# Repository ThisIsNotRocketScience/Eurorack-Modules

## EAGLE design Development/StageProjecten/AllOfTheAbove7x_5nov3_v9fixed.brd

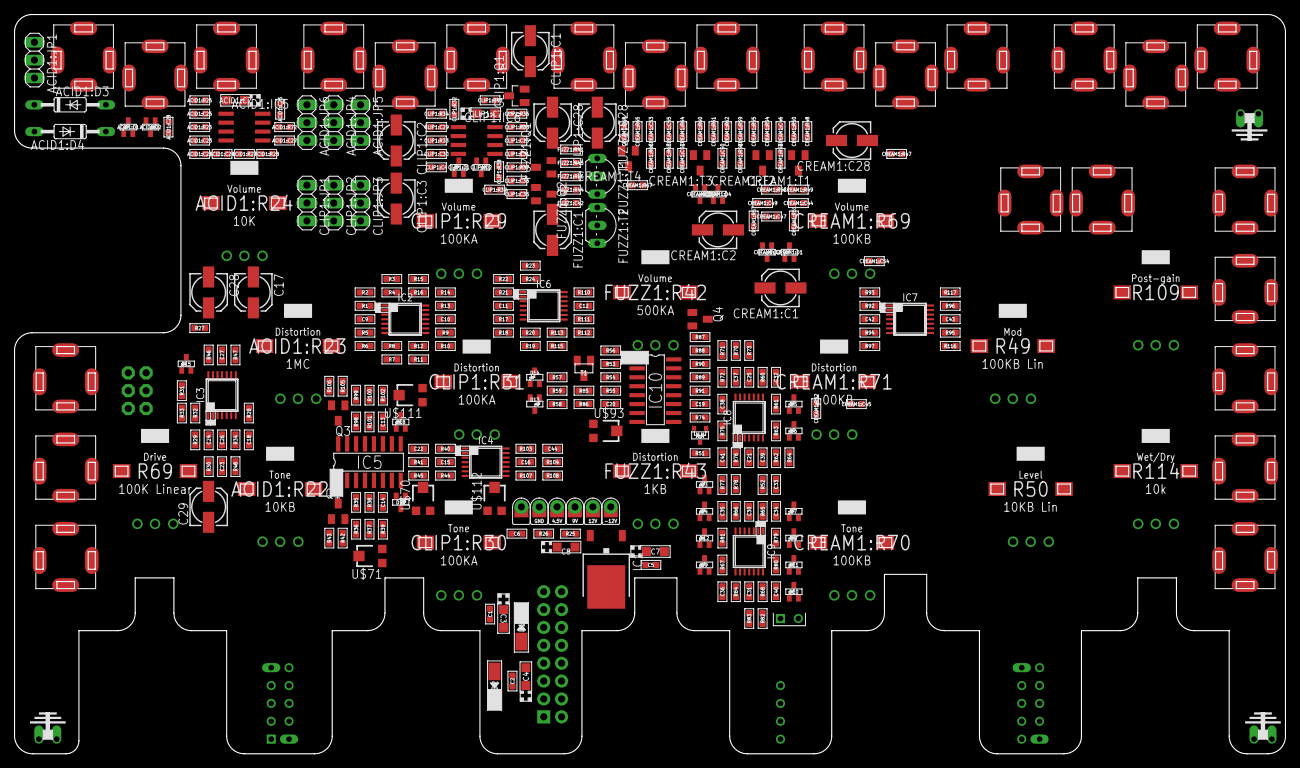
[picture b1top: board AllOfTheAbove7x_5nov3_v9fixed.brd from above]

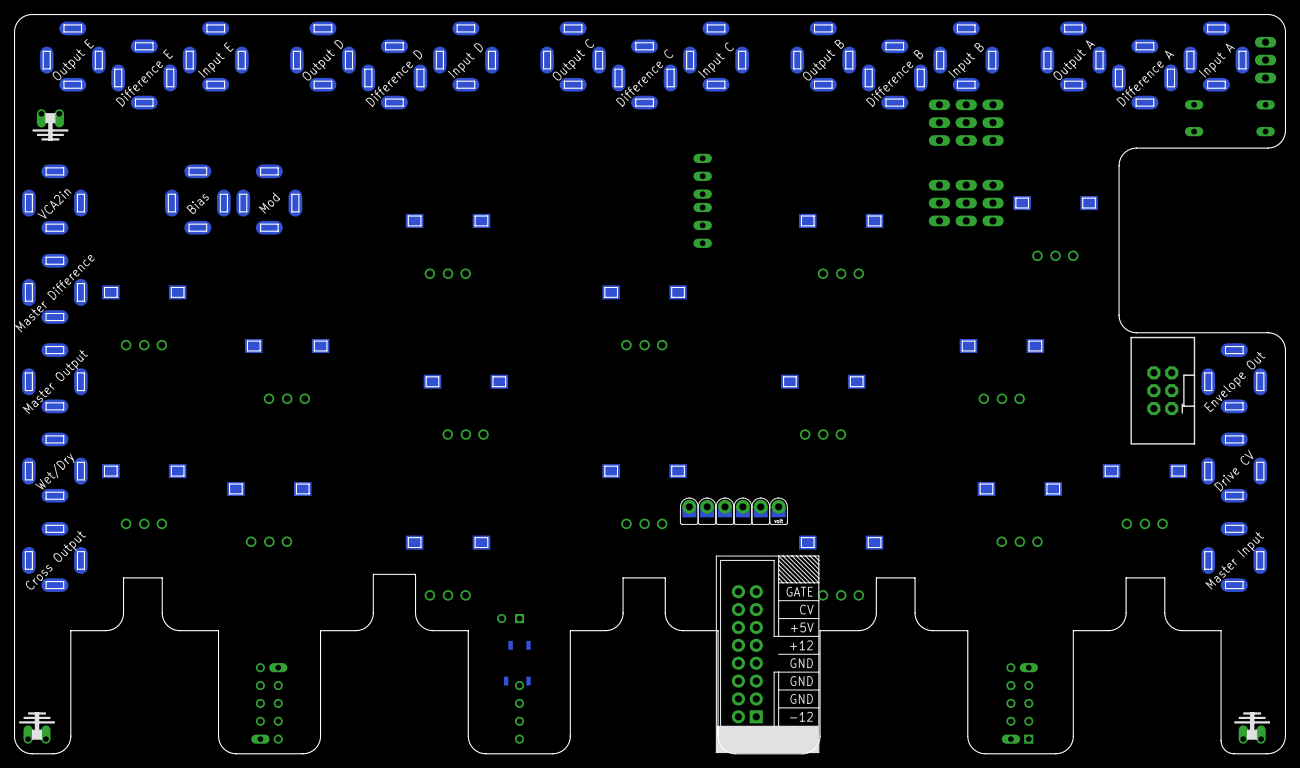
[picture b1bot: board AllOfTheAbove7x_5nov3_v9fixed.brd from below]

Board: 2 copper layers, 180.7 x 105.1 mm, 357 parts (2 on the bottom side), 204 nets, no tracks yet.

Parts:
12V: POWER12V; FENIXINTERNALCONNECTIONPAD
-12V: POWER-12V; FENIXINTERNALCONNECTIONPAD
ACID1:C7: 10uF; CASE-A_3216
ACID1:C22, ACID1:C28: 1nF; C0603
ACID1:C23: 10nF; C0603
ACID1:C24, ACID1:C25: 100n; C0603
ACID1:C26: 47nF; C0603
ACID1:C27: 1uF; C0603
ACID1:D1, ACID1:D2: BAS16W; SOT-323
ACID1:D3, ACID1:D4: 1N4148DO35-10; DO35-10
ACID1:IC5: UA741D; SO08
ACID1:JP1, ACID1:JP4, ACID1:JP5, ACID1:JP6: 1X03
ACID1:R22: 10KB; ALPS_POT_SQUAREHOLES
ACID1:R23: 1MC; ALPS_POT_SQUAREHOLES
ACID1:R24: 10K; ALPS_POT_SQUAREHOLES
ACID1:R25: 10K; R0603
ACID1:R26: 4.7K; R0603
ACID1:R27, ACID1:R72: 1M; R0603
ACID1:R28: 5.6K; R0603
C1, C2, C5, C6, C9, C10, C11, C12, C13, C14, C15, C16, C19, C20, C21, C25, C26, C27, C30, C31, C38, C42, C43: 100n; C0603
C3, C4, C7, C8: 10u; CASE-A_3216
C17, C28, C29: 10uF; 153CLV-0505
C18, C22, C23, C44: 10pF; C0603
C24: 47pF; C0603
C32, C34, C35, C36, C37: 33p; C0603
C33: 220p; C0603
C39: 680n; C0603
C40, C41: 33p FIX; C0603
CLIP1:C1, CLIP1:C3: 4.7uF; 153CLV-0505
CLIP1:C2: 2.2uF; 153CLV-0505
CLIP1:C4, CLIP1:C25: 100n; C0603
CLIP1:C7: 10uF; CASE-A_3216
CLIP1:C28: 1uF; 153CLV-0505
CLIP1:C29, CLIP1:C36: 22nF; C0603
CLIP1:C30: 1nF; C0603
CLIP1:C31: 100pF; C0603
CLIP1:C35: 3.3nF; C0603
CLIP1:D1, CLIP1:D2: BAS16W; SOT-323
CLIP1:IC6: UA741D; SO08
CLIP1:JP1, CLIP1:JP2, CLIP1:JP3: 1X03
CLIP1:Q1: SST201; SOT23
CLIP1:R29, CLIP1:R30, CLIP1:R31: 100KA; ALPS_POT_SQUAREHOLES
CLIP1:R32, CLIP1:R34, CLIP1:R39: 1M; R0603
CLIP1:R33, CLIP1:R37: 1K; R0603
CLIP1:R35: 560R; R0603
CLIP1:R36: 47R; R0603
CLIP1:R38: 1.5K; R0603
CLIP1:R40: 10K; R0603
CREAM1:C1, CREAM1:C2, CREAM1:C28: 1uF; 153CLV-0505
CREAM1:C44, CREAM1:C47, CREAM1:C50: 470pF; C0603
CREAM1:C45: 1uF; C0603
CREAM1:C46, CREAM1:C49, CREAM1:C53, CREAM1:C54: 100nF; C0603
CREAM1:C52: 4nF; C0603
CREAM1:C55: 10nF; C0603
CREAM1:D1, CREAM1:D2, CREAM1:D3, CREAM1:D4: BAS16W; SOT-323
CREAM1:R47, CREAM1:R63: 39K; R0603
CREAM1:R48: 47K; R0603
CREAM1:R49, CREAM1:R56, CREAM1:R61: 470K; R0603
CREAM1:R50: 100R; R0603
CREAM1:R51, CREAM1:R53, CREAM1:R57, CREAM1:R58, CREAM1:R62: 10K; R0603
CREAM1:R52: 1K; R0603
CREAM1:R54, CREAM1:R59, CREAM1:R65: 100K; R0603
CREAM1:R55, CREAM1:R60: 150R; R0603
CREAM1:R64: 22K; R0603
CREAM1:R66: 430K; R0603
CREAM1:R67: 15K; R0603
CREAM1:R68: 3.3K; R0603
CREAM1:R69, CREAM1:R70, CREAM1:R71: 100KB; ALPS_POT_SQUAREHOLES
CREAM1:T1, CREAM1:T2, CREAM1:T3, CREAM1:T4: 2n3904; SOT23-BEC
D1, D2: 1n4001; DO-214AC
D3, D4, D5, D6, D7, D8, D9, D10, D11, D12, D13, D14, D15, D17, D18: BAS16W; SOT-323
FUZZ1:C1: 20uF; 153CLV-0505
FUZZ1:C28: 2.2uF; 153CLV-0505
FUZZ1:C42: 10nF; C0603
FUZZ1:Q1, FUZZ1:Q2: MMBT3906LT1SMD; SOT23-BEC
FUZZ1:R41: 100K; R0603
FUZZ1:R42: 500KA; ALPS_POT_SQUAREHOLES
FUZZ1:R43: 1KB; ALPS_POT_SQUAREHOLES
FUZZ1:R44: 8.2K; R0603
FUZZ1:R45: 33K; R0603
FUZZ1:R46: 470R; R0603
FUZZ1:T1, FUZZ1:T2: TO92-EBC
GND: POWERGND; FENIXINTERNALCONNECTIONPAD
IC1: 7809DT; TO252
IC2, IC3, IC4, IC6, IC7, IC8, IC9: TL074TSSOP14; TSSOP14
IC5, IC10: LM13700M; SO16
J1, J3, J4, J5, J6, J7, J8, J9, J10, J11, J12, J13, J14, J15, J16, J17, J18, J19, J20, J21, J22, J23, J24, J25, J26: JACK; 3.5MM-JACK-SWITCH-13MM-NOHOLES
J2: POWERSHROUDED; POWER_16_SHROUDED
PCB1: EURORACK_PCB5STOMP; EURORACK36HP_5STOMP
Q1, Q3, Q4: MMBT3906LT1SMD; SOT23-BEC
R1, R2, R3, R4, R5, R6, R7, R8, R9, R10, R11, R12, R13, R14, R15, R16, R17, R18, R19, R20, R21, R22, R23, R24, R25, R26, R34, R48, R92, R93, R94, R95, R96, R97, R116, R117: 100k; R0603
R27: 1M; R0603
R28: 150K; R0603
R29, R42, R60, R72, R74, R105: 10K; R0603
R30: 470R; R0603
R31, R41, R47, R104: 1K; R0603
R32, R33, R38, R39, R40, R43, R44, R64, R65, R66, R67, R68, R71, R76, R78, R80, R83, R84, R101, R102, R103, R106, R107: 100K; R0603
R35, R98: 4.7K; R0603
R36, R37, R99, R100: 10R; R0603
R45, R46, R108: 330K; R0603
R49: 100KB Lin; ALPS_POT_SQUAREHOLES
R50: 10KB Lin; ALPS_POT_SQUAREHOLES
R51: 14; R0603
R52, R56: 470K; R0603
R53: 4K7; R0603
R54, R55, R70: 100; R0603
R57: 22K; R0603
R58, R62, R63, R77, R79, R81, R82: 33K; R0603
R59: 4M7; R0603
R61: 47K; R0603
R69: 100K Linear; ALPS_POT_SQUAREHOLES
R73: 220K; R0603
R75: 6K8; R0603
R85: 27k; R0603
R86: 150k; R0603
R87, R88: 1k; R0603
R89, R90: 200k; R0603
R91, R110: 47k; R0603
R109: ALPS_POT_SQUAREHOLES
R111: 2.2k; R0603
R112, R113: 18k; R0603
R114: 10k; ALPS_POT_SQUAREHOLES
R115: 14k; R0603
T1: 3906; SOT23-BEC
U$13, U$15, U$41, U$42, U$43, U$44: VOLTAGETESTPAD; POWERTESTPAD
U$22: 5STOMPBOARD; BYPASSBOARD
U$23: HEADPHONEHOLE_BIGGAP; HEADPHONEHOLE_GAP
U$48, U$49, U$50: GNDLOOP; GROUNDLOOP
U$68: HEADPHONE; 2X3-SHROUDED
U$70, U$71, U$111, U$112: 100k; TC33X
U$74: BAT54S; SOT23
U$92: TESTPOINT_DUAL_PTH; TESTPAD_DUAL_PTH
U$93: 50K; TC33X
WSOUT: SIGNALOUT; FENIXINTERNALCONNECTIONPAD

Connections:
4.5V: ACID1:R72.2, CLIP1:R34.2, R25.1, R26.2, U$44.P$1, U$44.P$2, U$44.P$3
9V: ACID1:JP4.1, C5.2, C7.+, CLIP1:JP2.1, CLIP1:Q1.1, CREAM1:R51.1, CREAM1:R57.1, CREAM1:R62.1, CREAM1:R66.2, CREAM1:R67.2, FUZZ1:C1.+, FUZZ1:Q1.E, FUZZ1:R42.P$1, FUZZ1:R43.P$1, FUZZ1:T1.E, IC1.2, R25.2, U$42.P$1, U$42.P$2, U$42.P$3
12V: 12V.P$1, ACID1:JP4.3, C1.2, C3.+, C6.2, C8.+, C9.2, C11.2, C13.2, C15.2, C19.2, C21.2, C26.2, C30.2, C42.2, CLIP1:JP2.3, D1.2, IC1.1, IC2.4, IC3.4, IC4.4, IC5.11, IC6.4, IC7.4, IC8.4, IC9.4, IC10.11, J21.SWITCH_B@1, J21.SWITCH_T@3, R50.P$3, R115.1, U$13.P$1, U$13.P$2, U$13.P$3, U$22.12V, U$70.3, U$71.3, U$93.1, U$111.3, U$112.3
-12V: -12V.P$1, ACID1:JP5.3, C2.1, C4.-, C10.1, C12.1, C14.1, C16.1, C20.1, C25.1, C27.1, C31.1, C43.1, CLIP1:JP3.3, D2.1, IC2.11, IC3.11, IC4.11, IC5.6, IC6.11, IC7.11, IC8.11, IC9.11, IC10.6, R56.2, R59.1, U$41.P$1, U$41.P$2, U$41.P$3, U$70.1, U$71.1, U$93.3, U$111.1, U$112.1
ACID1:N$2: ACID1:D3.C, ACID1:D4.A, ACID1:JP1.3
ACID1:N$3: ACID1:D1.CATHODE, ACID1:D2.ANODE, ACID1:JP1.1
ACID1:N$20: ACID1:C23.2, ACID1:R25.2
ACID1:N$21: ACID1:IC5.3, ACID1:JP6.2, ACID1:R25.1
ACID1:N$22: ACID1:C26.2, ACID1:IC5.2, ACID1:R27.1
ACID1:N$23: ACID1:C26.1, ACID1:R26.1
ACID1:N$32: ACID1:C27.1, ACID1:IC5.6, ACID1:R27.2
ACID1:N$33: ACID1:R23.P$3, ACID1:R26.2
ACID1:N$34: ACID1:C28.2, ACID1:JP1.2, ACID1:R22.P$3, ACID1:R24.P$3
ACID1:N$35: ACID1:C27.2, ACID1:R28.2
ACID1:N$36: ACID1:R22.P$1, ACID1:R22.P$2, ACID1:R28.1
ACID1:N$81: ACID1:C7.+, ACID1:C25.1, ACID1:IC5.7, ACID1:JP4.2
ACID1:N$82: ACID1:C24.1, ACID1:IC5.4, ACID1:JP5.2
ACID1:TO4.5V: ACID1:JP6.1, ACID1:R72.1
BIASINPUT: J23.TIP_B@1, J23.TIP_T@3, R61.2
BIASMAINLINE: C32.1, D4.ANODE, D6.ANODE, D8.ANODE, D9.ANODE, D10.ANODE, IC8.8, R60.1
CLIP1:N$37: CLIP1:C29.2, CLIP1:JP1.2, CLIP1:R33.1
CLIP1:N$38: CLIP1:C30.2, CLIP1:IC6.3, CLIP1:R33.2
CLIP1:N$39: CLIP1:C7.+, CLIP1:C25.1, CLIP1:IC6.7, CLIP1:JP2.2
CLIP1:N$40: CLIP1:C4.1, CLIP1:IC6.4, CLIP1:JP3.2
CLIP1:N$41: CLIP1:JP1.1, CLIP1:R34.1
CLIP1:N$42: CLIP1:C31.1, CLIP1:IC6.2, CLIP1:R31.P$1, CLIP1:R31.P$2, CLIP1:R35.2, CLIP1:R36.2
CLIP1:N$43: CLIP1:C1.+, CLIP1:C31.2, CLIP1:IC6.6, CLIP1:R31.P$3
CLIP1:N$44: CLIP1:C1.-, CLIP1:R37.1
CLIP1:N$45: CLIP1:D1.CATHODE, CLIP1:D2.ANODE, CLIP1:R30.P$1, CLIP1:R30.P$2, CLIP1:R37.2
CLIP1:N$46: CLIP1:R30.P$3, CLIP1:R38.1
CLIP1:N$47: CLIP1:C2.+, CLIP1:R36.1
CLIP1:N$48: CLIP1:C3.+, CLIP1:R35.1
CLIP1:N$49: CLIP1:C35.1, CLIP1:C36.1, CLIP1:R38.2
CLIP1:N$50: CLIP1:C36.2, CLIP1:Q1.3, CLIP1:R39.2
CLIP1:N$51: CLIP1:C28.+, CLIP1:Q1.2, CLIP1:R40.2
CLIP1:N$52: CLIP1:C28.-, CLIP1:R29.P$3
CREAM1:N$1: CREAM1:C28.-, CREAM1:R47.2
CREAM1:N$61: CREAM1:C28.+, CREAM1:C44.1, CREAM1:R48.2, CREAM1:R49.2, CREAM1:T1.B
CREAM1:N$62: CREAM1:R50.1, CREAM1:T1.E
CREAM1:N$63: CREAM1:C44.2, CREAM1:C45.1, CREAM1:R49.1, CREAM1:R51.2, CREAM1:T1.C
CREAM1:N$64: CREAM1:C45.2, CREAM1:R71.P$3
CREAM1:N$65: CREAM1:C1.-, CREAM1:C47.1, CREAM1:R53.2, CREAM1:R54.2, CREAM1:R56.2, CREAM1:T2.B
CREAM1:N$66: CREAM1:C1.+, CREAM1:D1.ANODE, CREAM1:D2.CATHODE
CREAM1:N$67: CREAM1:R55.2, CREAM1:T2.E
CREAM1:N$68: CREAM1:C47.2, CREAM1:C49.1, CREAM1:D1.CATHODE, CREAM1:D2.ANODE, CREAM1:R56.1, CREAM1:R57.2, CREAM1:T2.C
CREAM1:N$69: CREAM1:C49.2, CREAM1:R58.1
CREAM1:N$70: CREAM1:C2.-, CREAM1:C50.1, CREAM1:R58.2, CREAM1:R59.2, CREAM1:R61.2, CREAM1:T3.B
CREAM1:N$71: CREAM1:R60.2, CREAM1:T3.E
CREAM1:N$72: CREAM1:C50.2, CREAM1:C52.1, CREAM1:D3.ANODE, CREAM1:D4.CATHODE, CREAM1:R61.1, CREAM1:R62.2, CREAM1:R63.1, CREAM1:T3.C
CREAM1:N$73: CREAM1:C53.1, CREAM1:R70.P$2
CREAM1:N$74: CREAM1:C55.2, CREAM1:R63.2, CREAM1:R70.P$1
CREAM1:N$75: CREAM1:C52.2, CREAM1:R64.1, CREAM1:R70.P$3
CREAM1:N$76: CREAM1:C2.+, CREAM1:D3.CATHODE, CREAM1:D4.ANODE
CREAM1:N$77: CREAM1:C53.2, CREAM1:R65.2, CREAM1:R66.1, CREAM1:T4.B
CREAM1:N$78: CREAM1:C54.1, CREAM1:R67.1, CREAM1:T4.C
CREAM1:N$79: CREAM1:R68.2, CREAM1:T4.E
CREAM1:N$80: CREAM1:C54.2, CREAM1:R69.P$3
CREAM1:N$84: CREAM1:R52.1, CREAM1:R71.P$1
CREAM1:N$85: CREAM1:C46.2, CREAM1:R53.1
CREAM1:N$86: CREAM1:C46.1, CREAM1:R71.P$2
CROSSFADER_OUT: IC6.14, J26.TIP_B@1, J26.TIP_T@3, R110.1
CV_IN: J25.TIP_B@1, J25.TIP_T@3, R112.2
ENVELOPE_OUT: J1.SWITCH_B@1, J1.SWITCH_T@3, J24.TIP_B@1, J24.TIP_T@3, R47.1
EURORACK_IN: J20.TIP_B@1, J20.TIP_T@3, R34.1
FUZZ1:N$53: FUZZ1:Q2.E, FUZZ1:R41.1, FUZZ1:R43.P$3, FUZZ1:T2.E
FUZZ1:N$54: FUZZ1:C28.-, FUZZ1:Q1.B, FUZZ1:R41.2, FUZZ1:T1.B
FUZZ1:N$55: FUZZ1:Q1.C, FUZZ1:Q2.B, FUZZ1:R45.2, FUZZ1:T1.C, FUZZ1:T2.B
FUZZ1:N$56: FUZZ1:C1.-, FUZZ1:R43.P$2
FUZZ1:N$57: FUZZ1:C42.2, FUZZ1:R42.P$3
FUZZ1:N$58: FUZZ1:C42.1, FUZZ1:R44.1, FUZZ1:R46.2
FUZZ1:N$59: FUZZ1:Q2.C, FUZZ1:R44.2, FUZZ1:T2.C
GND: ACID1:C7.-, ACID1:C22.2, ACID1:C24.2, ACID1:C25.2, ACID1:C28.1, ACID1:D1.ANODE, ACID1:D2.CATHODE, ACID1:D3.A, ACID1:D4.C, ACID1:JP5.1, ACID1:R23.P$1, ACID1:R23.P$2, ACID1:R24.P$1, C1.1, C2.2, C3.-, C4.+, C5.1, C6.1, C7.-, C8.-, C9.1, C10.2, C11.1, C12.2, C13.1, C14.2, C15.1, C16.2, C17.-, C19.1, C20.2, C21.1, C23.1, C25.2, C26.1, C27.2, C29.-, C30.1, C31.2, C42.1, C43.2, CLIP1:C2.-, CLIP1:C3.-, CLIP1:C4.2, CLIP1:C7.-, CLIP1:C25.2, CLIP1:C30.1, CLIP1:C35.2, CLIP1:D1.ANODE, CLIP1:D2.CATHODE, CLIP1:JP3.1, CLIP1:R29.P$1, CLIP1:R32.2, CLIP1:R39.1, CLIP1:R40.1, CREAM1:C55.1, CREAM1:R48.1, CREAM1:R50.2, CREAM1:R52.2, CREAM1:R54.1, CREAM1:R55.1, CREAM1:R59.1, CREAM1:R60.1, CREAM1:R64.2, CREAM1:R65.1, CREAM1:R68.1, CREAM1:R69.P$1, D3.CATHODE, D5.CATHODE, D7.CATHODE, D11.CATHODE, D12.CATHODE, D13.ANODE, D14.ANODE, FUZZ1:R45.1, FUZZ1:R46.1, GND.P$1, IC1.3, IC4.5, IC4.10, IC5.7, IC5.10, IC6.10, IC6.12, IC7.3, IC7.5, IC7.10, IC7.12, IC8.5, IC8.10, IC10.7, IC10.10, J1.RING_B@1, J1.RING_T@3, J2.3, J2.4, J2.5, J2.6, J2.7, J2.8, J3.RING_B@1, J3.RING_T@3, J4.RING_B@1, J4.RING_T@3, J5.RING_B@1, J5.RING_T@3, J6.RING_B@1, J6.RING_T@3, J7.RING_B@1, J7.RING_T@3, J8.RING_B@1, J8.RING_T@3, J9.RING_B@1, J9.RING_T@3, J10.RING_B@1, J10.RING_T@3, J11.RING_B@1, J11.RING_T@3, J12.RING_B@1, J12.RING_T@3, J13.RING_B@1, J13.RING_T@3, J14.RING_B@1, J14.RING_T@3, J15.RING_B@1, J15.RING_T@3, J16.RING_B@1, J16.RING_T@3, J17.RING_B@1, J17.RING_T@3, J18.RING_B@1, J18.RING_T@3, J19.RING_B@1, J19.RING_T@3, J20.RING_B@1, J20.RING_T@3, J20.SWITCH_B@1, J20.SWITCH_T@3, J21.RING_B@1, J21.RING_T@3, J22.RING_B@1, J22.RING_T@3, J23.RING_B@1, J23.RING_T@3, J23.SWITCH_B@1, J23.SWITCH_T@3, J24.RING_B@1, J24.RING_T@3, J25.RING_B@1, J25.RING_T@3, J25.SWITCH_B@1, J25.SWITCH_T@3, J26.RING_B@1, J26.RING_T@3, R1.2, R5.2, R9.2, R13.2, R17.2, R21.2, R26.1, R27.1, R28.1, R36.1, R37.2, R39.2, R42.1, R46.1, R49.P$1, R50.P$1, R51.2, R52.2, R54.1, R55.1, R69.P$1, R72.2, R73.1, R74.1, R87.1, R88.1, R99.1, R100.2, R102.2, R105.1, R109.P$1, R114.P$1, U$22.GND, U$22.GND2, U$22.GND3, U$43.P$1, U$43.P$2, U$43.P$3, U$48.P$1, U$48.P$2, U$49.P$1, U$49.P$2, U$50.P$1, U$50.P$2, U$68.3, U$68.4, U$92.P$2
GUITAR_IN: C28.-, R27.2, U$68.5, U$68.6
GUITAR_OUT: R31.2, R32.2, U$15.P$1, U$15.P$2, U$15.P$3
INPUT_A: J6.TIP_B@1, J6.TIP_T@3, R2.2, U$22.P$3
INPUT_B: J4.TIP_B@1, J4.TIP_T@3, R6.2, U$22.P$7
INPUT_C: J11.TIP_B@1, J11.TIP_T@3, R10.2, U$22.P$11
INPUT_D: J14.TIP_B@1, J14.TIP_T@3, R14.2, U$22.P$15
INPUT_E: J17.TIP_B@1, J17.TIP_T@3, R22.2, U$22.P$19
INPUT_WS: R85.2, U$22.P$20
MIX_OUT: D15.ANODE, IC3.8, IC3.9, R35.1
unnamed: IC7.2, R92.2, R93.1
unnamed: D1.1, J2.9, J2.10
unnamed: D2.2, J2.1, J2.2
unnamed: ACID1:C22.1, ACID1:C23.1, U$22.P$4
unnamed: ACID1:R24.P$2, U$22.P$2
unnamed: IC7.1, J7.TIP_B@1, J7.TIP_T@3, R93.2
unnamed: CLIP1:C29.1, CLIP1:R32.1, U$22.P$8
unnamed: FUZZ1:C28.+, U$22.P$12
unnamed: FUZZ1:R42.P$2, U$22.P$10
unnamed: CREAM1:R47.1, U$22.P$16
unnamed: CREAM1:R69.P$2, U$22.P$14
unnamed: CLIP1:R29.P$2, U$22.P$6
unnamed: IC7.6, R94.2, R97.1
unnamed: C23.2, C28.+, IC3.3, R28.2
unnamed: IC2.3, R1.1, R2.1
unnamed: IC6.9, R111.2, R112.1, R113.1
unnamed: C24.1, IC3.1, R29.2, R31.1
unnamed: IC2.1, J8.TIP_B@1, J8.TIP_T@3, R4.1
unnamed: IC2.5, R5.1, R6.1
unnamed: IC2.6, R7.1, R8.2
unnamed: Q4.E, R111.1
unnamed: IC6.8, Q4.B
unnamed: IC2.7, J5.TIP_B@1, J5.TIP_T@3, R8.1
unnamed: IC2.10, R9.1, R10.1
unnamed: IC2.9, R11.1, R12.2
unnamed: R114.P$3, R115.2
unnamed: R113.2, R114.P$2
unnamed: IC2.8, J12.TIP_B@1, J12.TIP_T@3, R12.1
unnamed: IC2.12, R13.1, R14.1
unnamed: IC2.13, R15.1, R16.2
unnamed: IC7.7, J9.TIP_B@1, J9.TIP_T@3, R97.2
unnamed: IC7.9, R95.2, R116.1
unnamed: IC2.14, J15.TIP_B@1, J15.TIP_T@3, R16.1
unnamed: IC6.5, R17.1, R18.1
unnamed: IC6.6, R19.1, R20.2
unnamed: IC7.8, J13.TIP_B@1, J13.TIP_T@3, R116.2
unnamed: IC7.13, R96.2, R117.1
unnamed: IC6.7, J10.TIP_B@1, J10.TIP_T@3, R20.1
unnamed: IC6.3, R21.1, R22.1
unnamed: IC6.2, R23.1, R24.2
unnamed: IC7.14, J16.TIP_B@1, J16.TIP_T@3, R117.2
unnamed: IC6.1, J18.TIP_B@1, J18.TIP_T@3, R24.1
unnamed: C24.2, IC3.2, R29.1, R30.2
unnamed: C29.+, R30.1
unnamed: C18.2, IC3.7, R33.2, R48.2
unnamed: IC3.5, R34.2
unnamed: IC5.4, R37.1, R38.1
unnamed: IC5.3, R35.2, R36.2
unnamed: IC4.3, IC5.5, R39.1
unnamed: C22.1, IC4.2, R40.1
unnamed: C22.2, IC4.1, R40.2, R41.1
unnamed: R38.2, U$71.2
unnamed: D17.ANODE, IC4.7, Q1.B
unnamed: D17.CATHODE, IC4.6, R43.1, R44.2, R45.2
unnamed: Q1.E, R42.2, R43.2
unnamed: IC5.1, Q1.C
unnamed: R45.1, U$70.2
unnamed: R44.1, R69.P$2
unnamed: IC3.13, IC3.14, R47.2
unnamed: C17.+, D15.CATHODE, IC3.12, R46.2
unnamed: C18.1, IC3.6, R48.1
unnamed: R51.1, U$74.P$3
unnamed: C32.2, IC8.9, R60.2, R61.1
unnamed: R49.P$2, R57.2
unnamed: J22.TIP_B@1, J22.TIP_T@3, R49.P$3
unnamed: D14.CATHODE, R57.1, R58.1, R59.2, T1.E
unnamed: R50.P$2, R58.2
unnamed: C38.2, R74.2, R75.2, U$74.P$1, U$74.P$2
unnamed: C33.1, IC8.7, R62.1, R63.2, R64.2
unnamed: C33.2, C39.2, IC8.6, R62.2
unnamed: C39.1, IC10.5, R52.1
unnamed: D5.ANODE, D6.CATHODE, IC9.3, R63.1
unnamed: C34.1, IC9.1, R65.1, R79.2, R80.2
unnamed: D7.ANODE, D8.CATHODE, IC9.5, R79.1
unnamed: C34.2, IC9.2, R64.1, R65.2
unnamed: C35.2, IC9.6, R66.2, R80.1
unnamed: C35.1, IC9.7, R66.1, R67.2, R81.2
unnamed: D9.CATHODE, D12.ANODE, IC9.10, R81.1
unnamed: C36.1, IC9.8, R82.2, R83.2, R84.1
unnamed: C36.2, IC9.9, R67.1, R84.2
unnamed: D10.CATHODE, D11.ANODE, IC9.12, R82.1
unnamed: C40.2, IC9.13, R68.2, R83.1
unnamed: C40.1, IC9.14, R68.1, R77.1, R78.1
unnamed: D3.ANODE, D4.CATHODE, IC8.3, R77.2
unnamed: C41.2, IC8.2, R76.1, R78.2
unnamed: C41.1, IC8.1, R75.1, R76.2, U$92.P$1
unnamed: C38.1, IC8.12, R73.2
unnamed: C37.1, IC8.14, R70.2
unnamed: C37.2, IC8.13, R71.2, R72.1
unnamed: D13.CATHODE, R56.1, T1.B
unnamed: R53.1, T1.C
unnamed: IC10.1, R53.2
unnamed: IC10.3, R54.2, R85.1
unnamed: R86.2, U$93.2
unnamed: IC10.4, R55.2, R86.1
unnamed: IC10.13, R87.2, R89.1
unnamed: IC10.14, R88.2, R90.1
unnamed: IC5.13, R100.1, R101.1
unnamed: IC5.14, R98.2, R99.2
unnamed: IC4.12, IC5.12, R102.1
unnamed: C44.1, IC4.13, R103.1
unnamed: C44.2, IC4.14, R103.2, R104.1
unnamed: R101.2, U$111.2
unnamed: D18.ANODE, IC4.8, Q3.B
unnamed: D18.CATHODE, IC4.9, R106.1, R107.2, R108.2
unnamed: Q3.E, R105.2, R106.2
unnamed: IC5.16, Q3.C
unnamed: R108.1, U$112.2
unnamed: R107.1, R109.P$2
unnamed: IC2.2, R3.1, R4.2
OTA_CONTROL: IC10.16, Q4.C
OTA_OUT: IC6.13, IC10.12, R91.2, R110.2
OUTPUT_A: J4.SWITCH_B@1, J4.SWITCH_T@3, R3.2, R92.1, U$22.P$1
OUTPUT_B: J11.SWITCH_B@1, J11.SWITCH_T@3, R7.2, R94.1, U$22.P$5
OUTPUT_C: J14.SWITCH_B@1, J14.SWITCH_T@3, R11.2, R95.1, U$22.P$9
OUTPUT_D: J17.SWITCH_B@1, J17.SWITCH_T@3, R15.2, R96.1, U$22.P$13
OUTPUT_E: R23.2, R98.1, U$22.P$17
OUTPUT_WS: R70.1, R71.1, U$22.P$18, WSOUT.P$1
VCA_CV_IN1: J21.TIP_B@1, J21.TIP_T@3, R69.P$3
VCA_CV_IN2: J1.TIP_B@1, J1.TIP_T@3, R109.P$3
VCA_OUTPUT1: J6.SWITCH_B@1, J6.SWITCH_T@3, R18.2, R41.2, R90.2
VCA_OUTPUT2: J3.TIP_B@1, J3.TIP_T@3, R19.2, R89.2, R91.1, R104.2
VCA_SIG_IN: IC3.10, R32.1, R33.1

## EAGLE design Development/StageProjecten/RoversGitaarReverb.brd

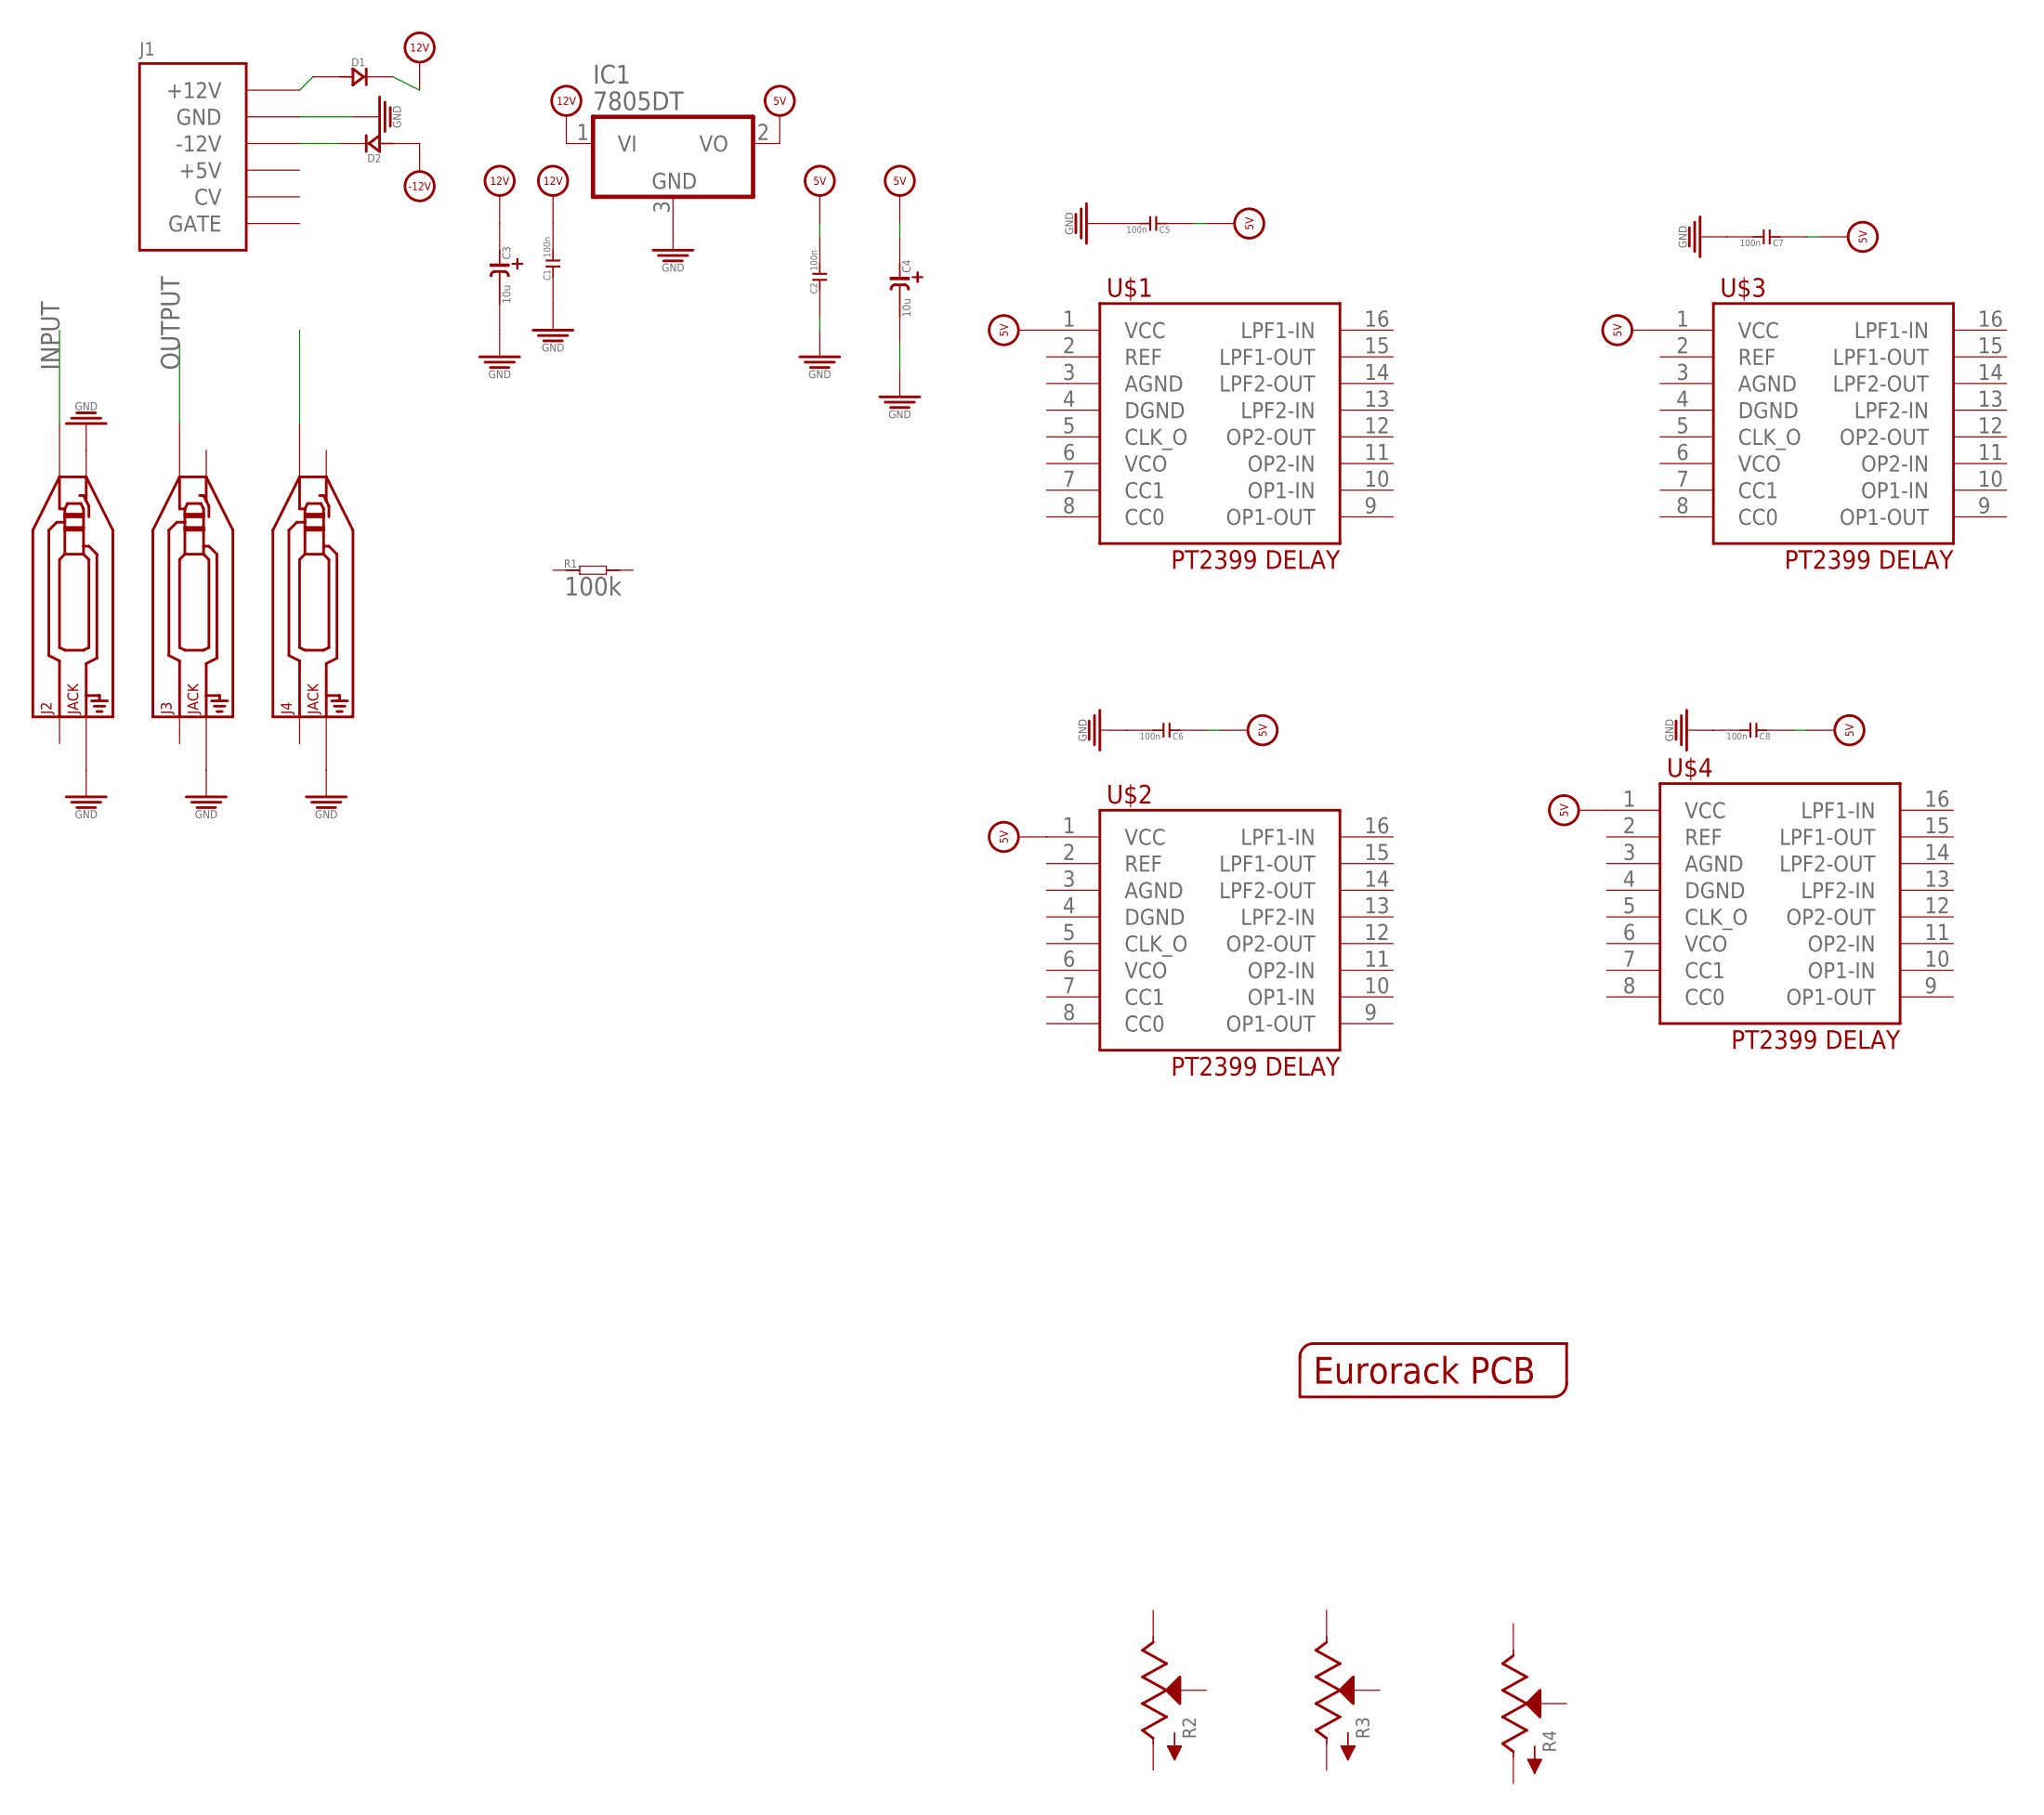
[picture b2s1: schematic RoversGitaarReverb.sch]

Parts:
C1, C2, C5, C6, C7, C8: 100n; C0603
C3, C4: 10u; CASE-A_3216
D1, D2: D-SMA; DO-214AC
IC1: 7805DT; TO252
J1: POWERSHROUDED; POWER_16_SHROUDED
J2, J3, J4: JACK; 3.5MM-JACK-SWITCH-13MM-NOHOLES
PCB1: EURORACK_PCB12HP; EURORACK12HPPCB
R1: 100k; R0603
R2, R3, R4: POTSQUAREHOLE_SMALLKNOB; ALPS_POT_SQUAREHOLES
U$1, U$2, U$3, U$4: PT2399; SO16

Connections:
5V: C2.2, C4.+ (1), C5.1, C6.1, C7.1, C8.1, IC1.2 (VO), U$1.1 (VCC), U$2.1 (VCC), U$3.1 (VCC), U$4.1 (VCC)
12V: C1.2, C3.+ (1), D1.2 (-), IC1.1 (VI)
-12V: D2.1 (+)
GND: C1.1, C2.1, C3.- (2), C4.- (2), C5.2, C6.2, C7.2, C8.2, IC1.3 (GND), J1.3 (GND), J1.4 (GND), J1.5 (GND), J1.6 (GND), J1.7 (GND), J1.8 (GND), J2.RING_B@1 (RING), J2.RING_T@3 (RING), J2.SWITCH_B@1 (SWITCH), J2.SWITCH_T@3 (SWITCH), J3.RING_B@1 (RING), J3.RING_T@3 (RING), J4.RING_B@1 (RING), J4.RING_T@3 (RING)
INPUT: J2.TIP_B@1 (TIP), J2.TIP_T@3 (TIP)
unnamed: D1.1 (+), J1.9 (+12V), J1.10 (+12V)
unnamed: D2.2 (-), J1.1 (-12V), J1.2 (-12V)
unnamed: J4.TIP_B@1 (TIP), J4.TIP_T@3 (TIP)
OUTPUT: J3.TIP_B@1 (TIP), J3.TIP_T@3 (TIP)

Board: 2 copper layers, 24 parts (1 on the bottom side), 8 nets, no tracks yet.

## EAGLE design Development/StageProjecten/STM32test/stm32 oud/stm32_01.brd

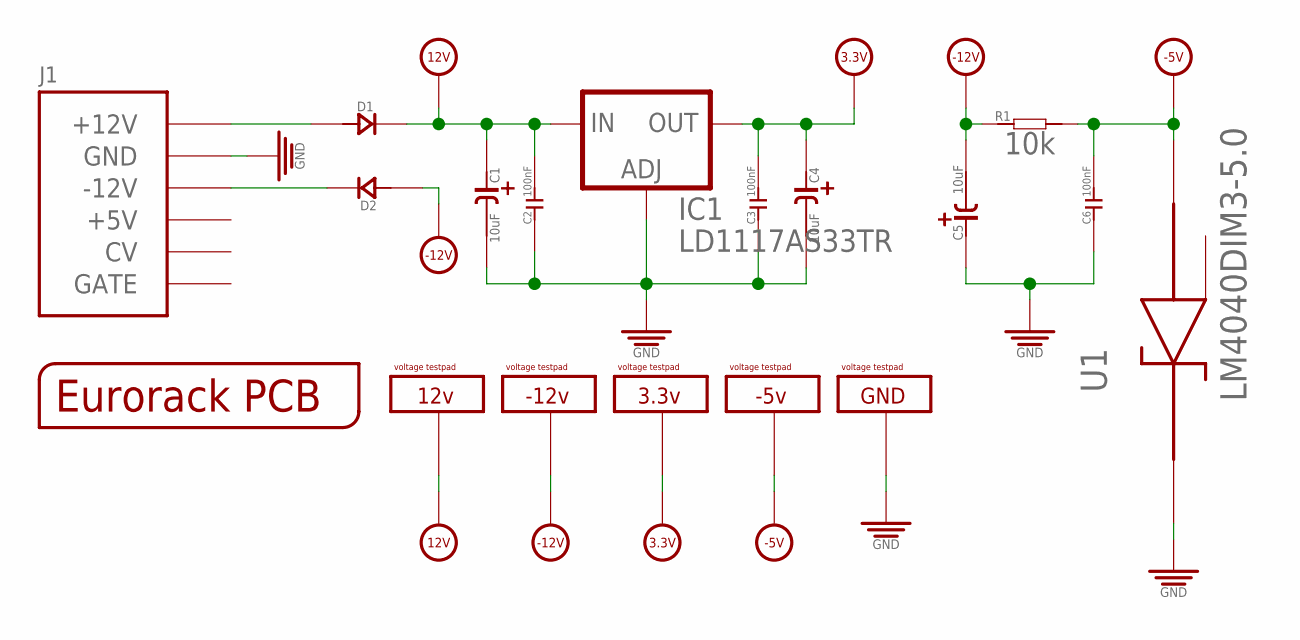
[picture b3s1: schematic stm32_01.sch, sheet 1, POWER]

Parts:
C1, C4, C5: 10uF; CASE-A_3216
C2, C3, C6: 100nF; C0603
D1, D2: D-SMA; DO-214AC
IC1: LD1117AS33TR; SOT223
J1: POWERSHROUDED; POWER_16_SHROUDED
PCB1: EURORACK_PCB12HP; EURORACK12HPPCB
R1: 10k; R0603
U1: LM4040DIM3-5.0; SOT95P237X112-3N
U$7, U$8, U$37, U$38, U$43: VOLTAGETESTPAD; POWERTESTPAD

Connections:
3.3V: C3.2, C4.+ (1), IC1.2 (OUT), IC1.4 (OUT), U$37.P$1, U$37.P$2, U$37.P$3; also elsewhere on the board
12V: C1.+ (1), C2.2, D1.2 (-), IC1.3 (IN), U$7.P$1, U$7.P$2, U$7.P$3; also elsewhere on the board
-5V: C6.2, R1.2, U1.2 (ANODE), U$38.P$1, U$38.P$2, U$38.P$3; also elsewhere on the board
-12V: C5.- (2), D2.1 (+), R1.1, U$8.P$1, U$8.P$2, U$8.P$3; also elsewhere on the board
GND: C1.- (2), C2.1, C3.1, C4.- (2), C5.+ (1), C6.1, IC1.1 (ADJ), J1.3 (GND), J1.4 (GND), J1.5 (GND), J1.6 (GND), J1.7 (GND), J1.8 (GND), U1.1 (CATHODE), U$43.P$1, U$43.P$2, U$43.P$3; also elsewhere on the board
unnamed: D2.2 (-), J1.1 (-12V), J1.2 (-12V)
unnamed: D1.1 (+), J1.9 (+12V), J1.10 (+12V)

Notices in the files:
parts and their libraries:
SparkFun-Connectors: Licensing: CC v3.0 Share-Alike You are welcome to use this library for commercial purposes.
